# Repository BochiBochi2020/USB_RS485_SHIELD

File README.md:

# USB_RS485_SHIELD
JMRIのCMRI NodeへRS485を通して接続するためのArduino shieldです。 RS485の通信は、独自仕様のRJ45のコネクタを使用しています。 
現在、全面的に見直しを行っています。
主な変更点は以下となります。
* USBの接続は、micro USBに変更。
* DC-Jackから、12Vの電源を取得
* 12Vは、arduino shieldのVinへ供給

USB Hubは市販のものが使えますが、好みに応じて別途USB Hub shieldも
設計しています。
また、CMRIのノードとして、keypad、在線センサ/列車センサー、ポイント制御及び
信号機を鋭意作成中です。

/以上/

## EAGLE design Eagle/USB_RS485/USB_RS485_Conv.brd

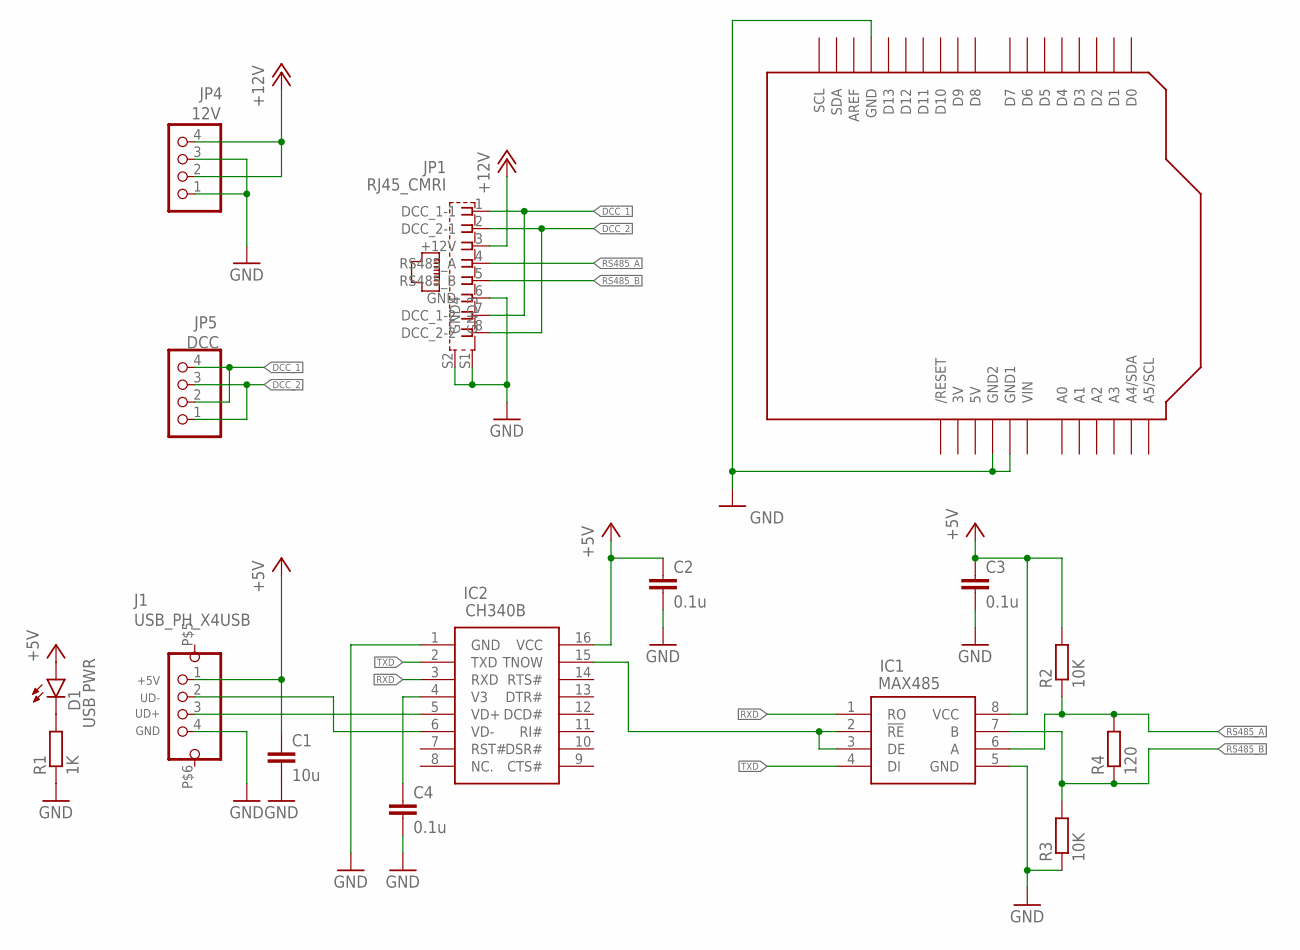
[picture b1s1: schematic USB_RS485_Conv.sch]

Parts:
C1: 10u; C1206
C2, C3, C4: 0.1u; C1206
D1: USB PWR; LED_SMD_1608
IC1: MAX485; SOIC127P600X175-8N
IC2: CH340B; SOIC127P600X177-16N
J1: USB_PH_X4USB; USB_PH_04/90
JP1: RJ45_CMRI; RJ45_7810
JP4: 12V; 1X04/90
JP5: DCC; 1X04/90
Q1: ARDUINO-SHIELD-NOTEXT; ARDUINO-SHIELD
R1: 1K; R1206
R2, R3: 10K; R1206
R4: 120; R1206

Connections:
+5V: C1.1, C2.1, C3.1, D1.A, IC1.8 (VCC), IC2.16 (VCC), J1.1, R2.2
+12V: JP1.3 (+12V), JP4.2, JP4.4
DCC_1: JP1.1 (DCC_1-1), JP1.7 (DCC_1-2), JP5.2, JP5.4
DCC_2: JP1.2 (DCC_2-1), JP1.8 (DCC_2-2), JP5.1, JP5.3
GND: C1.2, C2.2, C3.2, C4.2, IC1.5 (GND), IC2.1 (GND), J1.4, JP1.6 (GND), JP1.S1 (GND3), JP1.S2 (GND4), JP4.1, JP4.3, Q1.GND, Q1.GND1, Q1.GND2, R1.1, R3.1
unnamed: IC2.5 (VD+), J1.3
unnamed: IC2.6 (VD-), J1.2
unnamed: C4.1, IC2.4 (V3)
unnamed: IC1.2 (!RE), IC1.3 (DE), IC2.15 (TNOW)
unnamed: D1.C (K), R1.2
RS485_A: IC1.6 (A), JP1.4 (RS485_A), R2.1, R4.2
RS485_B: IC1.7 (B), JP1.5 (RS485_B), R3.2, R4.1
RXD: IC1.1 (RO), IC2.3 (RXD)
TXD: IC1.4 (DI), IC2.2 (TXD)

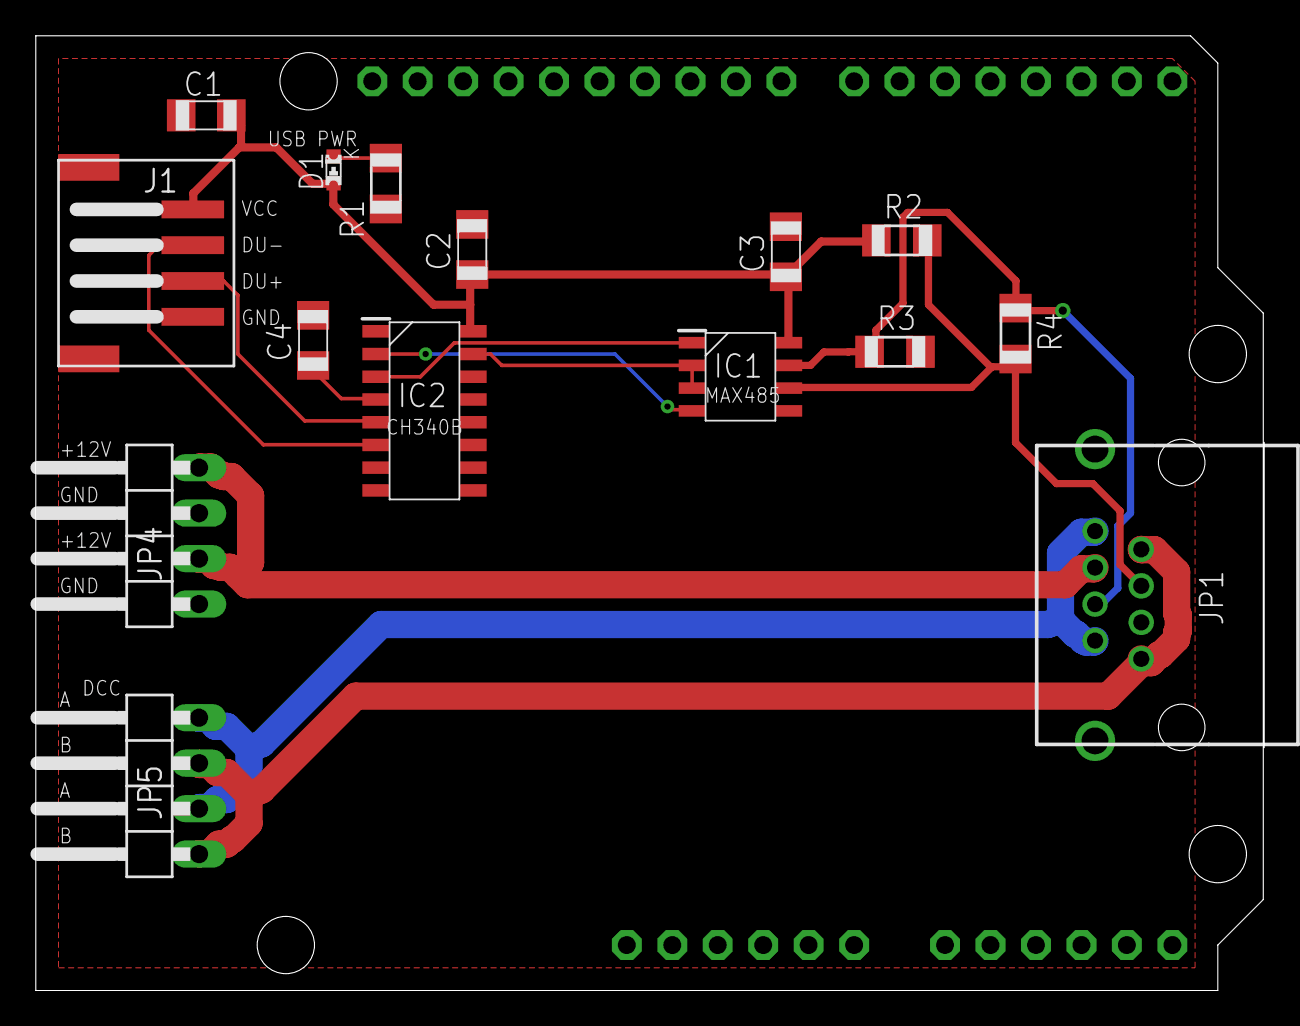
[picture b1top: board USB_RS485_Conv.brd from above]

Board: 2 copper layers, 68.6 x 53.3 mm, 16 parts (0 on the bottom side), 14 nets.

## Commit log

2022-03-26 add Eagle files
2024-01-10 rename branch
2024-01-10 rm Eagle
2024-01-11 try commit
